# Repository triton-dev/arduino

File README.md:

# Arduino

Eagle .lbr for some missing Arduino components, borads and others...

Contents

- Arduino Pro Micro
- LM35
- I2C LCD controller head pin
- DS1307 RTC IC
- I2C RTC EEPROM pinhead

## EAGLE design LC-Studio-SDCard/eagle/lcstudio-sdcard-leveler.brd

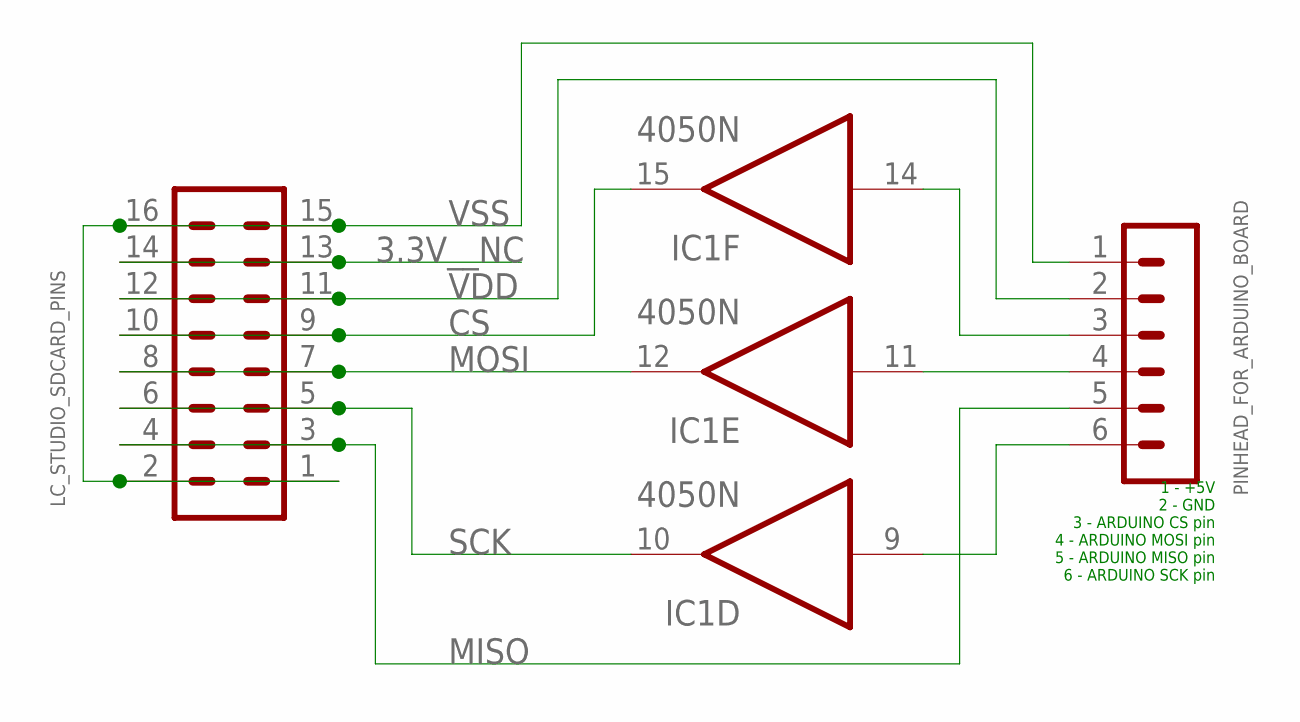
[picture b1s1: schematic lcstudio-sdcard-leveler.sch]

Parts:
IC1: 4050N; DIL16
LC_STUDIO_SDCARD_PINS: MA08-2
PINHEAD_FOR_ARDUINO_BOARD: MA06-1

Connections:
3.3V__NC: LC_STUDIO_SDCARD_PINS.13, LC_STUDIO_SDCARD_PINS.14
A-CS: IC1.14 (I), PINHEAD_FOR_ARDUINO_BOARD.3
CS: IC1.15 (O), LC_STUDIO_SDCARD_PINS.9, LC_STUDIO_SDCARD_PINS.10
MISO: LC_STUDIO_SDCARD_PINS.3, LC_STUDIO_SDCARD_PINS.4, PINHEAD_FOR_ARDUINO_BOARD.5
MOSI: IC1.12 (O), LC_STUDIO_SDCARD_PINS.7, LC_STUDIO_SDCARD_PINS.8
unnamed: IC1.9 (I), PINHEAD_FOR_ARDUINO_BOARD.6
unnamed: IC1.11 (I), PINHEAD_FOR_ARDUINO_BOARD.4
SCK: IC1.10 (O), LC_STUDIO_SDCARD_PINS.5, LC_STUDIO_SDCARD_PINS.6
VDD: IC1.1 (VDD), LC_STUDIO_SDCARD_PINS.11, LC_STUDIO_SDCARD_PINS.12, PINHEAD_FOR_ARDUINO_BOARD.2
VSS: IC1.8 (VSS), LC_STUDIO_SDCARD_PINS.1, LC_STUDIO_SDCARD_PINS.2, LC_STUDIO_SDCARD_PINS.15, LC_STUDIO_SDCARD_PINS.16, PINHEAD_FOR_ARDUINO_BOARD.1

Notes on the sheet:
1 - +5V 2 - GND 3 - ARDUINO CS pin 4 - ARDUINO MOSI pin 5 - ARDUINO MISO pin 6 - ARDUINO SCK pin

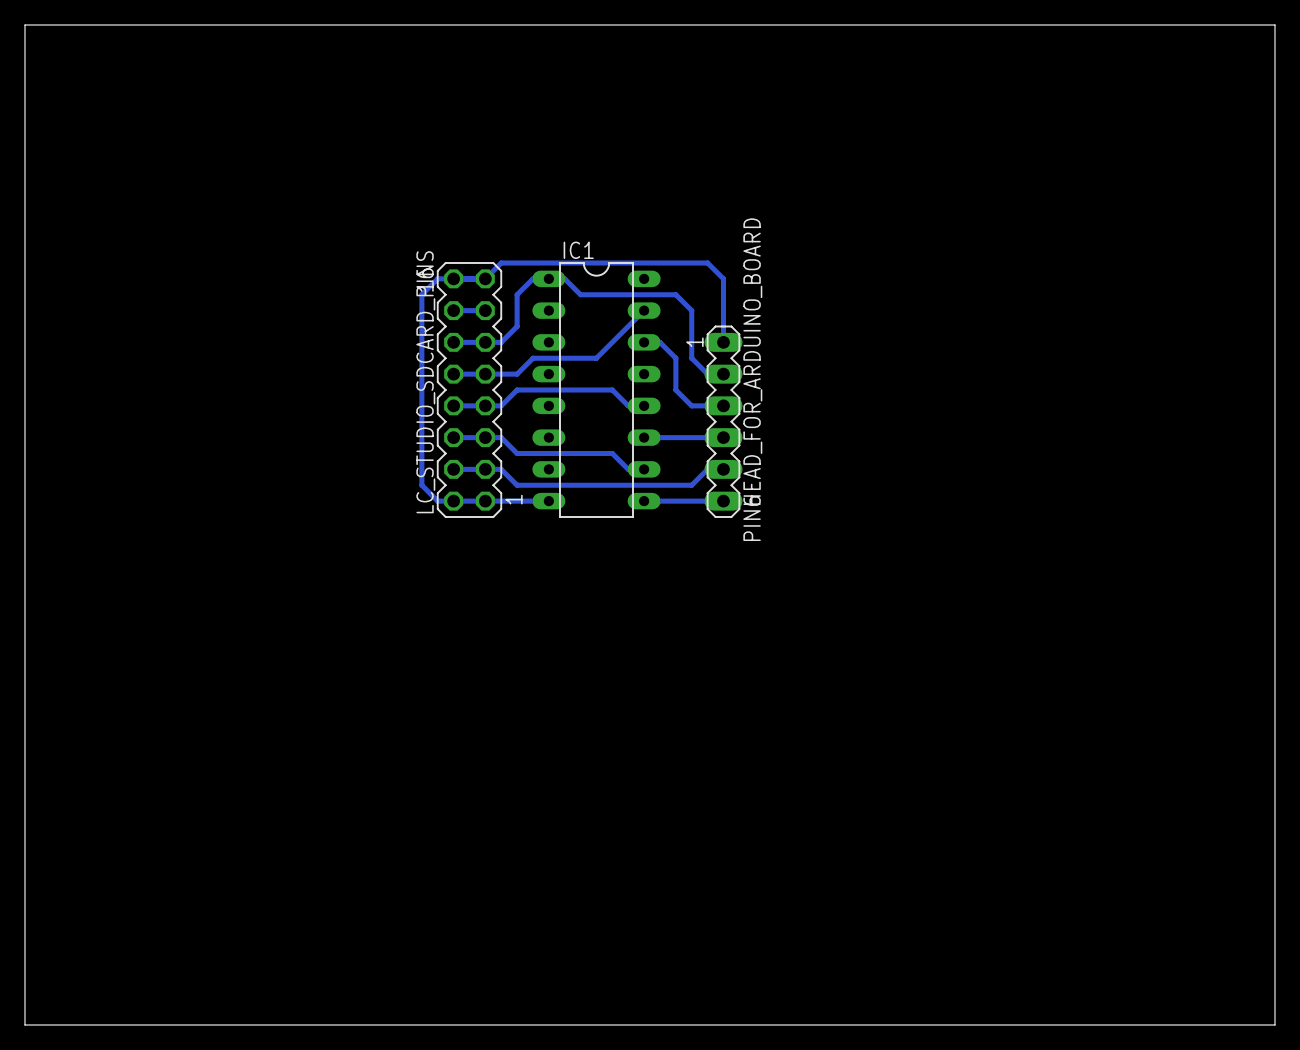
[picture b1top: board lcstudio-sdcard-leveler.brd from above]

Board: 2 copper layers, 100.0 x 80.0 mm, 3 parts (0 on the bottom side), 10 nets.

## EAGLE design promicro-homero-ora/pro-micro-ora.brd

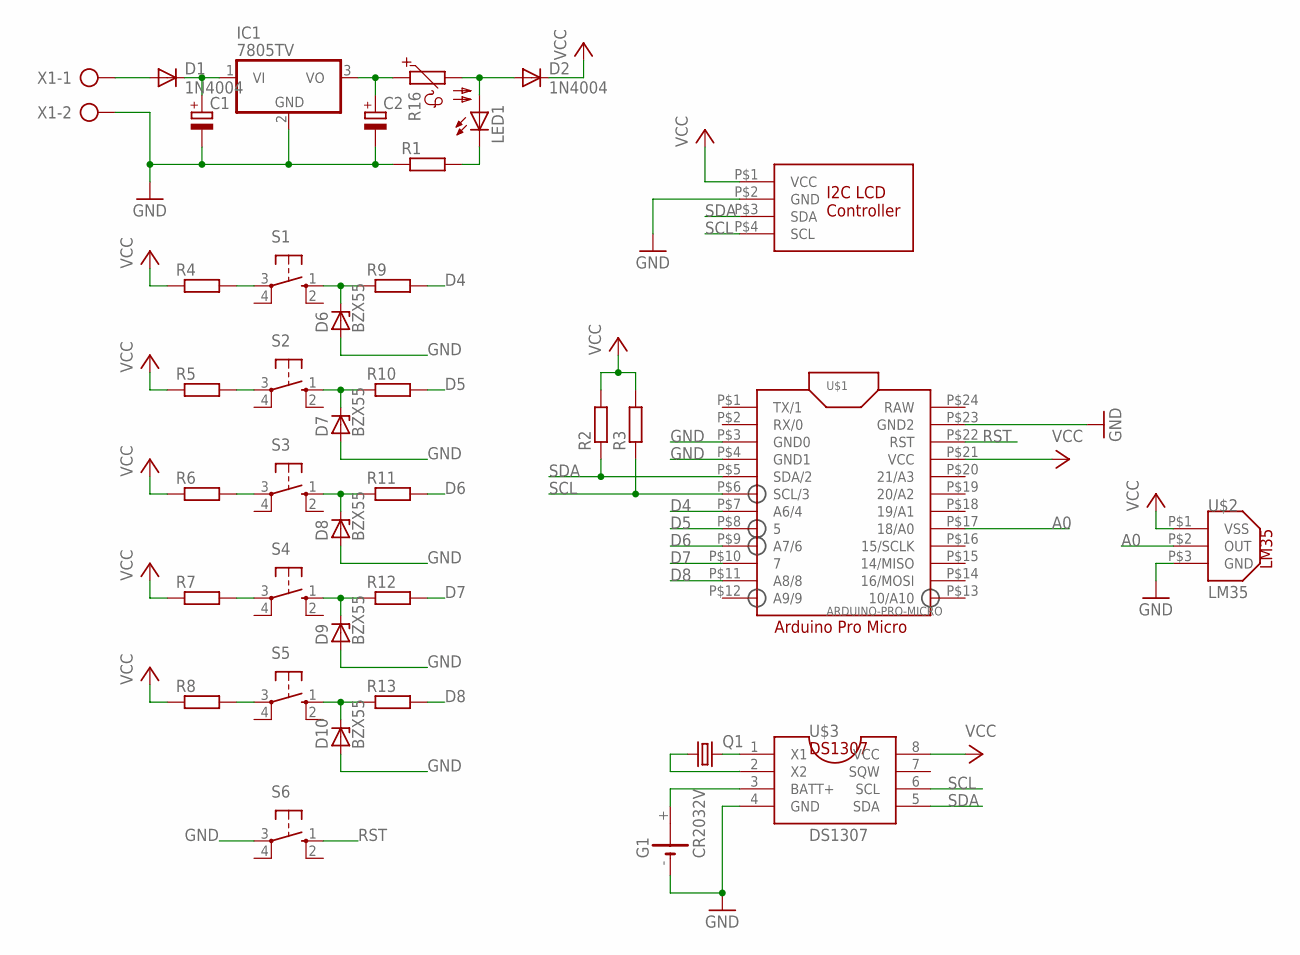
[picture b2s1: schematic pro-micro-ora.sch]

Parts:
C1, C2: CPOL-EUE2.5-5; E2,5-5
D1, D2: 1N4004; DO41-10
D6, D7, D8, D9, D10: BZX55; DO35Z10
G1: CR2032V
IC1: 7805TV; TO220V
LED1: LED5MM
Q1: CRYSTALTC26H; TC26H
R1, R2, R3, R4, R5, R6, R7, R8, R9, R10, R11, R12, R13: R-EU_0204/7; 0204/7
R16: PTC660; P660
S1, S2, S3, S4, S5, S6: 10-XX; B3F-10XX
U$1: ARDUINO-PRO-MICRO
U$2: LM35
U$3: DS1307
U$4: I2C_LCD
X1: AK500/2

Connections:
A0: U$1.P$17 (18/A0), U$2.P$2 (OUT)
D4: R9.2, U$1.P$7 (A6/4)
D5: R10.2, U$1.P$8 (5)
D6: R11.2, U$1.P$9 (A7/6)
D7: R12.2, U$1.P$10 (7)
D8: R13.2, U$1.P$11 (A8/8)
GND: C1.-, C2.-, D6.A, D7.A, D8.A, D9.A, D10.A, G1.-, IC1.2 (GND), R1.1, S6.3, U$1.P$3 (GND0), U$1.P$4 (GND1), U$1.P$23 (GND2), U$2.P$3 (GND), U$3.4 (GND), U$4.P$2 (GND), X1.2
unnamed: D1.A, X1.1
unnamed: C1.+, D1.C, IC1.1 (VI)
unnamed: D2.A, LED1.A, R16.2
unnamed: LED1.K (C), R1.2
unnamed: C2.+, IC1.3 (VO), R16.1
unnamed: R4.2, S1.3
unnamed: R5.2, S2.3
unnamed: R6.2, S3.3
unnamed: R7.2, S4.3
unnamed: R8.2, S5.3
unnamed: D6.C, R9.1, S1.1 (S)
unnamed: D7.C, R10.1, S2.1 (S)
unnamed: D8.C, R11.1, S3.1 (S)
unnamed: D9.C, R12.1, S4.1 (S)
unnamed: D10.C, R13.1, S5.1 (S)
unnamed: Q1.1, U$3.2 (X2)
unnamed: Q1.2, U$3.1 (X1)
unnamed: G1.+, U$3.3 (BATT+)
RAW: U$1.P$24 (RAW)
RST: S6.1 (S), U$1.P$22 (RST)
SCL: R3.1, U$1.P$6 (SCL/3), U$3.6 (SCL), U$4.P$4 (SCL)
SDA: R2.1, U$1.P$5 (SDA/2), U$3.5 (SDA), U$4.P$3 (SDA)
VCC: D2.C, R2.2, R3.2, R4.1, R5.1, R6.1, R7.1, R8.1, U$1.P$21 (VCC), U$2.P$1 (VSS), U$3.8 (VCC), U$4.P$1 (VCC)

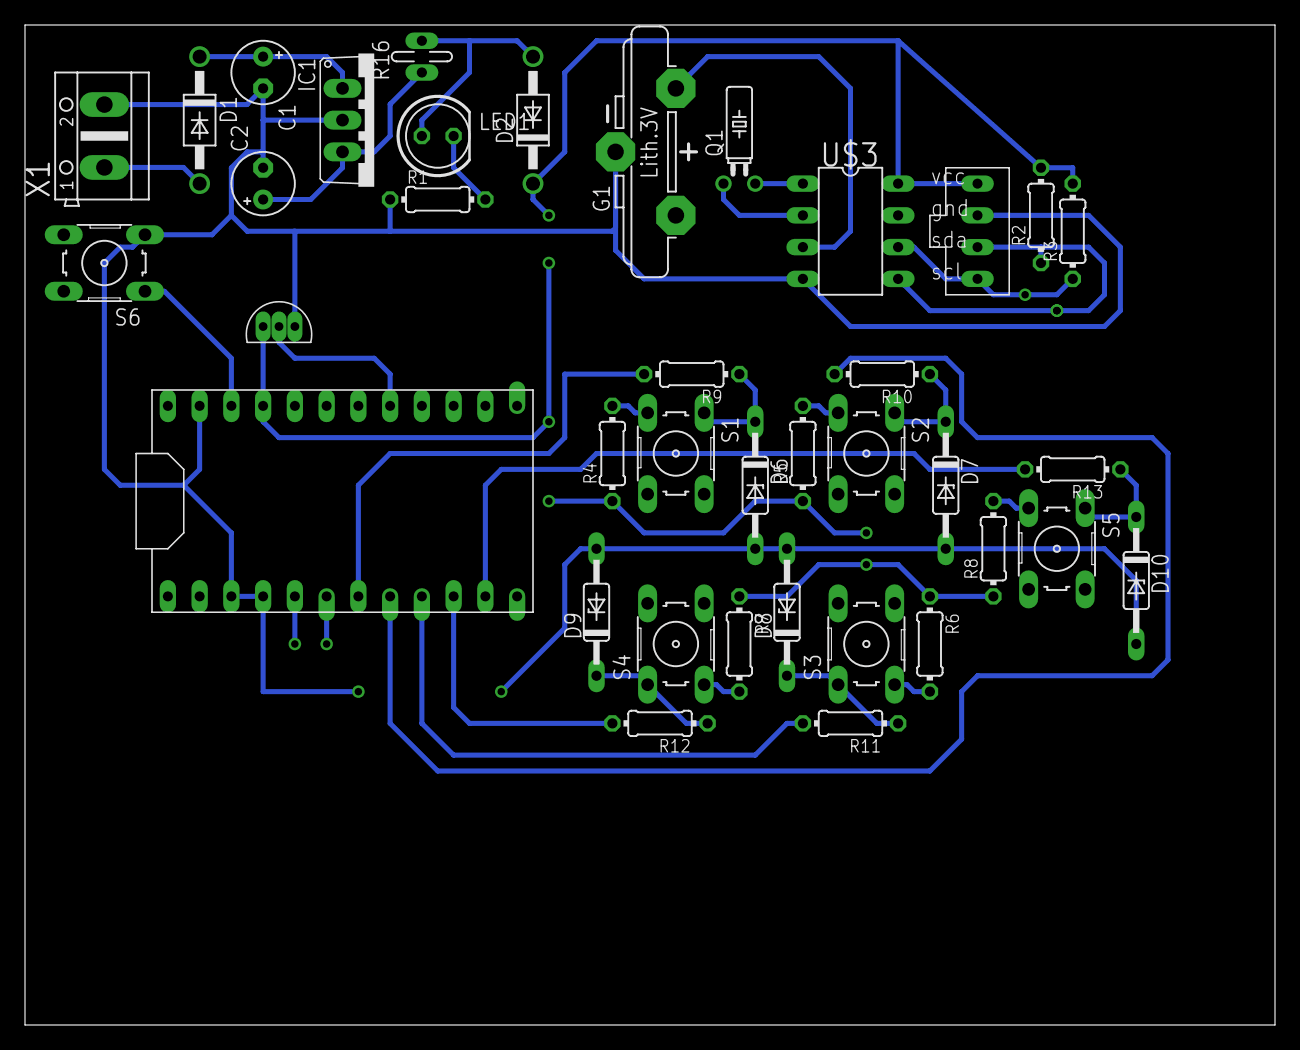
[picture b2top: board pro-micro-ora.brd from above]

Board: 2 copper layers, 100.0 x 80.0 mm, 38 parts (0 on the bottom side), 29 nets.

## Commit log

2016-10-21 LM35
    LM35 high precision temperature sensor.
2016-10-21 Arduino Pro Micro
    Arduino Pro Micro board to PCB.
2016-10-21 I2C LCD controller
    I2C LCD Controller
2016-10-21 DS1307 RTC
    DS1307 RTC
2016-10-21 ds1307 desc.
2016-10-21 I2C LCD Controller desc.
2016-10-21 Rename i2c-lcd-controller to i2c-lcd-controller.md
2016-10-21 Arduino-Pro-Micro desc.
2016-10-21 LM35 desc.
2016-10-21 More contents...
2016-10-21 Pro Micro hőmérő, óra
2016-10-21 Hőmérő és óra
2016-10-21 Pin mod
2016-10-26 i2c RTC EEPROM pinhead
2016-10-26 LM35 lbr
2016-10-26 New library struct.
2016-10-26 mv LM35 to folder
2016-10-26 add pro micro image
2016-10-26 add image
2016-10-26 mod text
2016-10-26 add md file
2016-10-27 add .md
2016-10-27 add eagle files
2016-10-27 add schematic
2016-10-28 pro micro pins
2016-10-28 add pins png
